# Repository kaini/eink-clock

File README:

# E-Ink Clock

For details read [the articles on my website](https://me.pushrax.com/e-ink-clock/).

## Build Instructions

To be able to successfully build the project you need the `inkscape` and
`magick` executable and a ARM GCC toolchain in your path. The resulting binary
is ready to be flashed onto the controller.

```
cd timekeeper
xargo build --target lpc1227-none-eabi --release
```

To execute the tests, run `cargo test`.

There are some features you might want to activate.

* `semihosted`: Enable debug output via the semihosting mechanism.
* `fake_time`: Do not wait for a valid DCF77 time, but just assume a hardcoded time value.
* `stay_awake`: Panic instead of going into Deep Power-Down mode.

## Warning

The PCB layout is not up to date!

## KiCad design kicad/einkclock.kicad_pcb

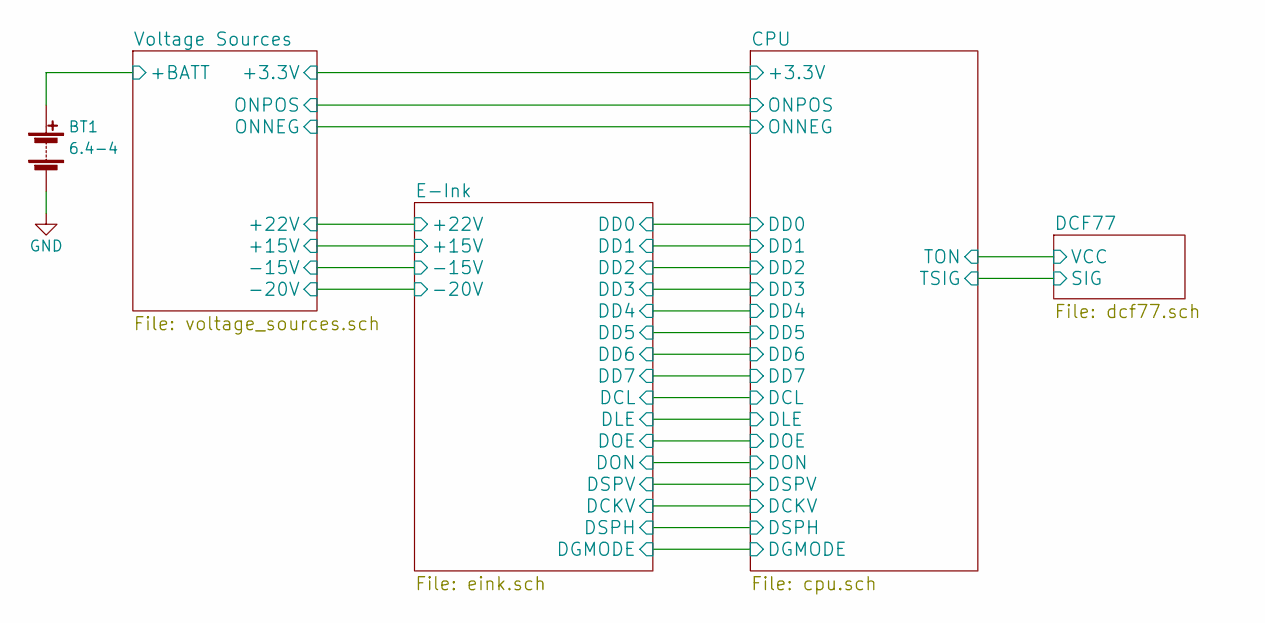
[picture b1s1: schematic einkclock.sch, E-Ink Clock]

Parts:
BT1: 6.4-4; WireConnection_1.00mmDrill

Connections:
GND: BT1.2 (-); also elsewhere on the board

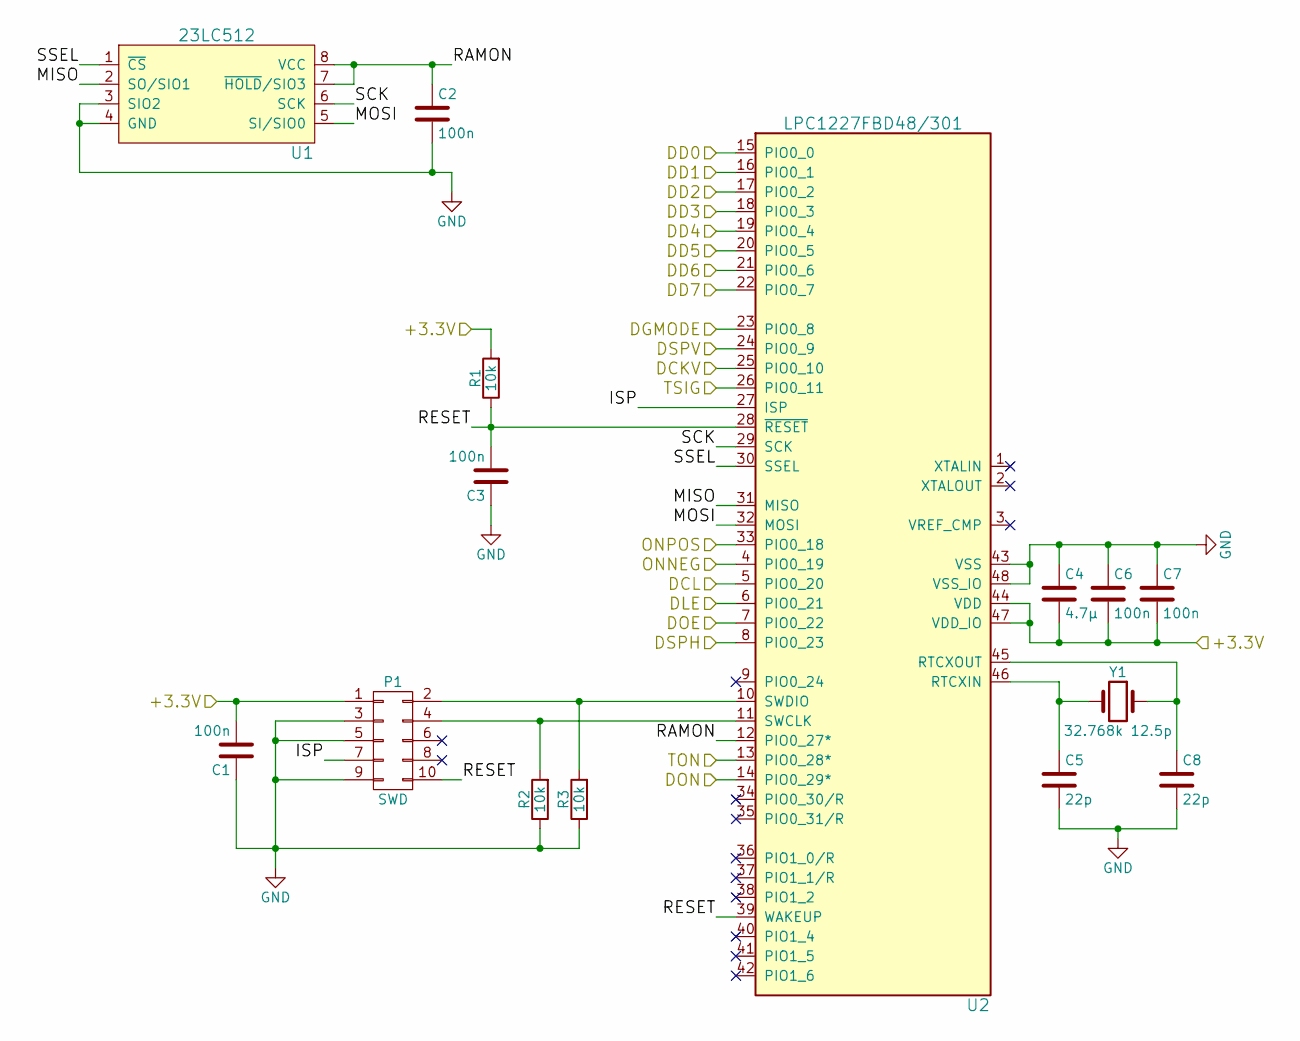
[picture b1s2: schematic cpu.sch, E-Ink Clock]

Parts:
C1, C2, C3, C6, C7: 100n; R_0805_HandSoldering
C4: 4.7µ; R_0805_HandSoldering
C5, C8: 22p; R_0805_HandSoldering
P1: SWD; IDC_Header_Straight_10pins
R1, R2, R3: 10k; R_0805_HandSoldering
U1: 23LC512; SOIC-8_3.9x4.9mm_Pitch1.27mm
U2: LPC1227FBD48/301; LQFP-48_7x7mm_Pitch0.5mm
Y1: 32.768k 12.5p; Crystal_Lying_1

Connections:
/CPU/+3.3V: C1.2, C4.2, C6.2, C7.2, P1.1, R1.2, U2.44 (VDD), U2.47 (VDD_IO); also elsewhere on the board
/CPU/DCKV: U2.25 (PIO0_10); also elsewhere on the board
/CPU/DCL: U2.5 (PIO0_20); also elsewhere on the board
/CPU/DD0: U2.15 (PIO0_0); also elsewhere on the board
/CPU/DD1: U2.16 (PIO0_1); also elsewhere on the board
/CPU/DD2: U2.17 (PIO0_2); also elsewhere on the board
/CPU/DD3: U2.18 (PIO0_3); also elsewhere on the board
/CPU/DD4: U2.19 (PIO0_4); also elsewhere on the board
/CPU/DD5: U2.20 (PIO0_5); also elsewhere on the board
/CPU/DD6: U2.21 (PIO0_6); also elsewhere on the board
/CPU/DD7: U2.22 (PIO0_7); also elsewhere on the board
/CPU/DGMODE: U2.23 (PIO0_8); also elsewhere on the board
/CPU/DLE: U2.6 (PIO0_21); also elsewhere on the board
/CPU/DOE: U2.7 (PIO0_22); also elsewhere on the board
/CPU/DON: U2.14 (PIO0_29*); also elsewhere on the board
/CPU/DSPH: U2.8 (PIO0_23); also elsewhere on the board
/CPU/DSPV: U2.24 (PIO0_9); also elsewhere on the board
/CPU/ISP: P1.7, U2.27 (ISP)
/CPU/MISO: U1.2 (SO/SIO1), U2.31 (MISO)
/CPU/MOSI: U1.5 (SI/SIO0), U2.32 (MOSI)
/CPU/ONPOS: U2.33 (PIO0_18); also elsewhere on the board
/CPU/RAMON: C2.1, U1.7 (~HOLD~/SIO3), U1.8 (VCC), U2.12 (PIO0_27*)
/CPU/RESET: C3.2, P1.10, R1.1, U2.28 (~RESET), U2.39 (WAKEUP)
/CPU/SCK: U1.6 (SCK), U2.29 (SCK)
/CPU/SSEL: U1.1 (~CS), U2.30 (SSEL)
/CPU/TON: U2.13 (PIO0_28*); also elsewhere on the board
/DCF77/SIG: U2.26 (PIO0_11); also elsewhere on the board
GND: C1.1, C2.2, C3.1, C4.1, C5.2, C6.1, C7.1, C8.2, P1.3, P1.5, P1.9, R2.1, R3.1, U1.3 (SIO2), U1.4 (GND), U2.43 (VSS), U2.48 (VSS_IO); also elsewhere on the board
unnamed: C5.1, U2.46 (RTCXIN), Y1.2
unnamed: C8.1, U2.45 (RTCXOUT), Y1.1
unnamed: P1.2, R3.2, U2.10 (SWDIO)
unnamed: P1.4, R2.2, U2.11 (SWCLK)

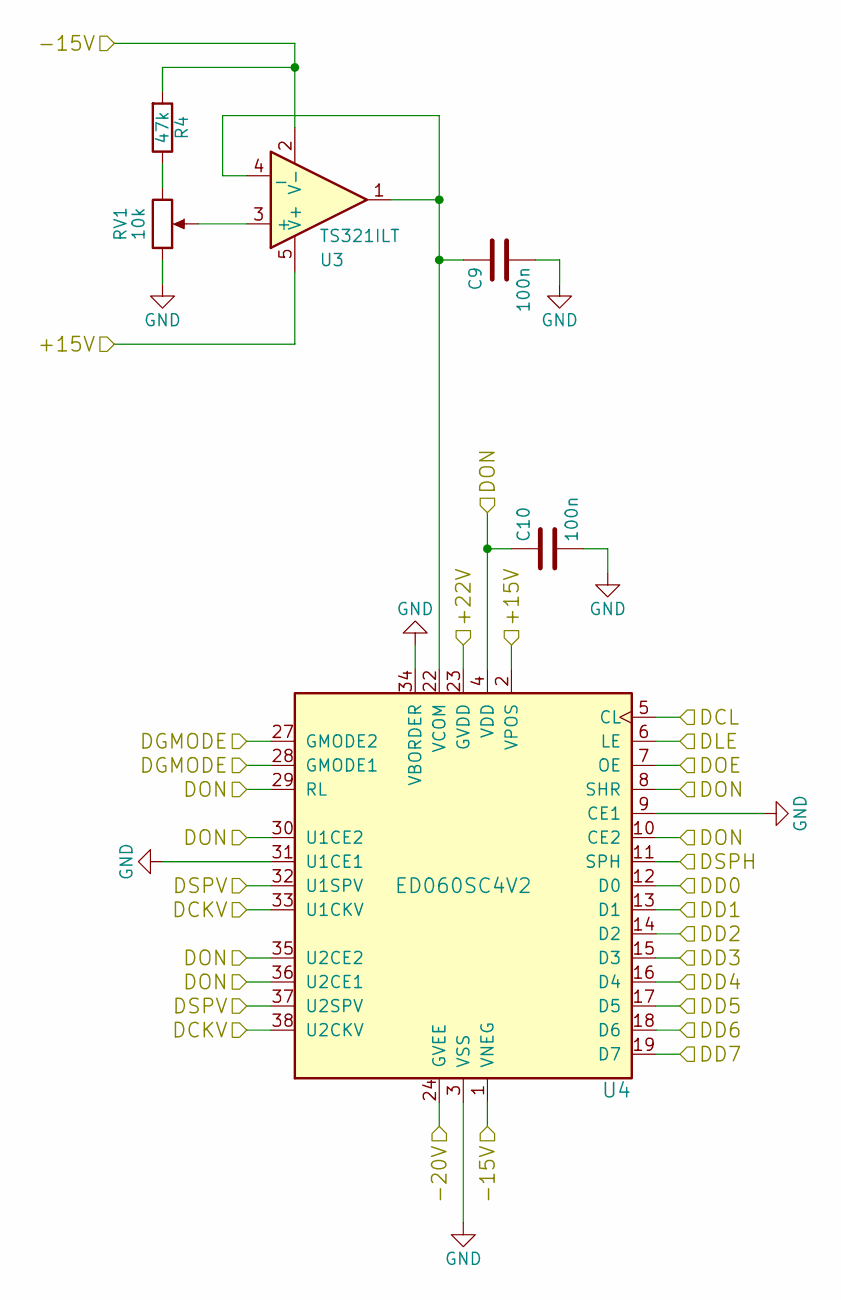
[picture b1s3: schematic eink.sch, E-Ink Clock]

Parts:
C9, C10: 100n; R_0805_HandSoldering
R4: 47k; R_0805_HandSoldering
RV1: 10k; Potentiometer_Trimmer_Vishay_TS53YL
U3: TS321ILT; SOT-23-5_HandSoldering
U4: ED060SC4V2; Hirose_FH26-39S-0.3SHW

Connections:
/CPU/DCKV: U4.33 (U1CKV), U4.38 (U2CKV); also elsewhere on the board
/CPU/DCL: U4.5 (CL); also elsewhere on the board
/CPU/DD0: U4.12 (D0); also elsewhere on the board
/CPU/DD1: U4.13 (D1); also elsewhere on the board
/CPU/DD2: U4.14 (D2); also elsewhere on the board
/CPU/DD3: U4.15 (D3); also elsewhere on the board
/CPU/DD4: U4.16 (D4); also elsewhere on the board
/CPU/DD5: U4.17 (D5); also elsewhere on the board
/CPU/DD6: U4.18 (D6); also elsewhere on the board
/CPU/DD7: U4.19 (D7); also elsewhere on the board
/CPU/DGMODE: U4.27 (GMODE2), U4.28 (GMODE1); also elsewhere on the board
/CPU/DLE: U4.6 (LE); also elsewhere on the board
/CPU/DOE: U4.7 (OE); also elsewhere on the board
/CPU/DON: C10.1, U4.4 (VDD), U4.8 (SHR), U4.10 (CE2), U4.29 (RL), U4.30 (U1CE2), U4.35 (U2CE2), U4.36 (U2CE1); also elsewhere on the board
/CPU/DSPH: U4.11 (SPH); also elsewhere on the board
/CPU/DSPV: U4.32 (U1SPV), U4.37 (U2SPV); also elsewhere on the board
/E-Ink/+15V: U3.5 (V+), U4.2 (VPOS); also elsewhere on the board
/E-Ink/+22V: U4.23 (GVDD); also elsewhere on the board
/E-Ink/-15V: R4.2, U3.2 (V-), U4.1 (VNEG); also elsewhere on the board
/E-Ink/-20V: U4.24 (GVEE); also elsewhere on the board
GND: C9.2, C10.2, RV1.1, U4.3 (VSS), U4.9 (CE1), U4.31 (U1CE1), U4.34 (VBORDER); also elsewhere on the board
unnamed: C9.1, U3.1, U3.4 (_), U4.22 (VCOM)
unnamed: R4.1, RV1.3
unnamed: RV1.2, U3.3 (+)

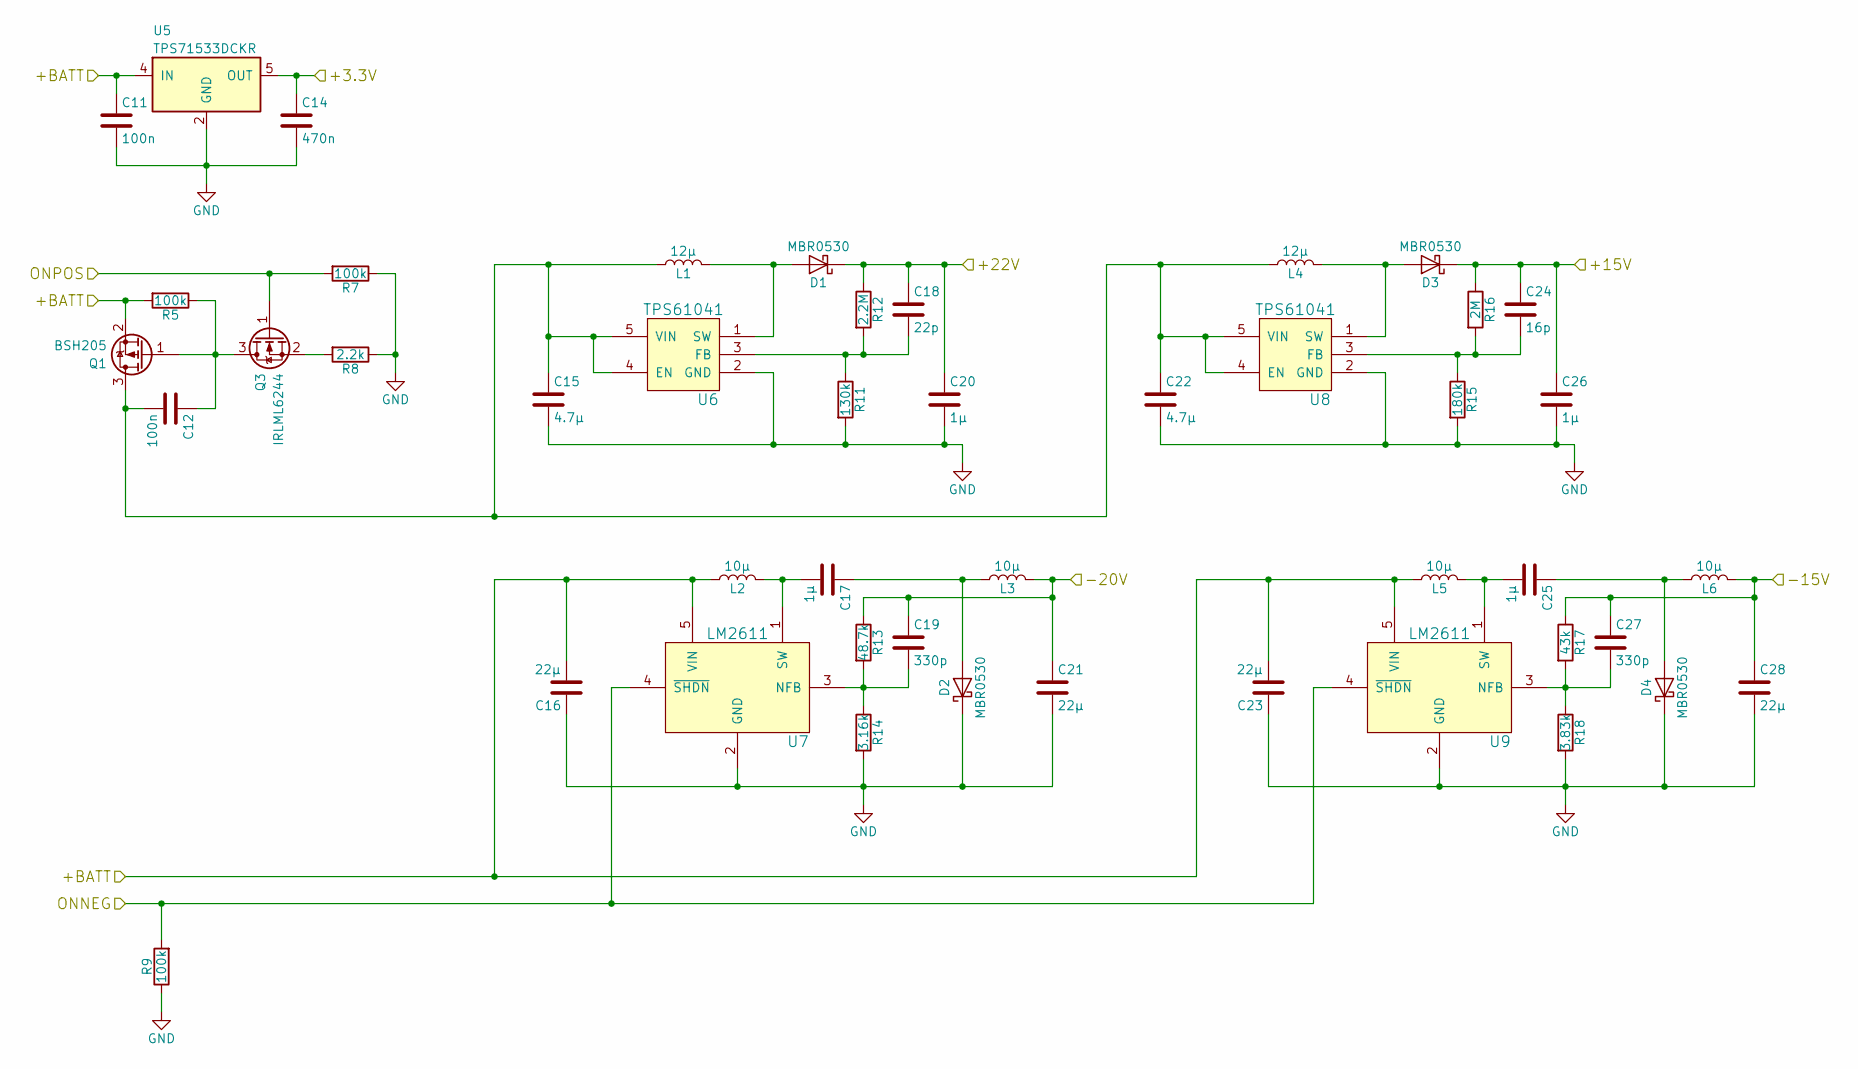
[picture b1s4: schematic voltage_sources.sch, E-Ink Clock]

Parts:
C11, C12: 100n; R_0805_HandSoldering
C14: 470n; R_0805_HandSoldering
C15, C22: 4.7µ; R_0805_HandSoldering
C16, C21, C23, C28: 22µ; R_0805_HandSoldering
C17, C20, C25, C26: 1µ; R_0805_HandSoldering
C18: 22p; R_0805_HandSoldering
C19, C27: 330p; R_0805_HandSoldering
C24: 16p; R_0805_HandSoldering
D1, D2, D3, D4: MBR0530; D_SOD-123
L1, L4: 12µ; Bourns_Inductor_SDR0703
L2, L3, L5, L6: 10µ; Inductor_TAIYO_YUDEN_3225
Q1: BSH205; SOT-23_Handsoldering
Q3: IRLML6244; SOT-23_Handsoldering
R5, R7, R9: 100k; R_0805_HandSoldering
R8: 2.2k; R_0805_HandSoldering
R11: 130k; R_0805_HandSoldering
R12: 2.2M; R_0805_HandSoldering
R13: 48.7k; R_0805_HandSoldering
R14: 3.16k; R_0805_HandSoldering
R15: 180k; R_0805_HandSoldering
R16: 2M; R_0805_HandSoldering
R17: 43k; R_0805_HandSoldering
R18: 3.83k; R_0805_HandSoldering
U5: TPS71533DCKR; SOT-353_SC-70-5_Handsoldering
U6, U8: TPS61041; SOT-23-5_HandSoldering
U7, U9: LM2611; SOT-23-5_HandSoldering

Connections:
/CPU/+3.3V: C14.1, U5.5 (OUT); also elsewhere on the board
/CPU/ONPOS: Q3.1 (G), R7.2; also elsewhere on the board
/E-Ink/+15V: C24.1, C26.1, D3.1 (K), R16.1; also elsewhere on the board
/E-Ink/+22V: C18.1, C20.1, D1.1 (K), R12.1; also elsewhere on the board
/E-Ink/-15V: C27.1, C28.1, L6.2, R17.1; also elsewhere on the board
/E-Ink/-20V: C19.1, C21.1, L3.2, R13.1; also elsewhere on the board
GND: C11.2, C14.2, C15.2, C16.1, C20.2, C21.2, C22.2, C23.1, C26.2, C28.2, D2.1 (K), D4.1 (K), R7.1, R8.1, R9.1, R11.2, R14.2, R15.2, R18.2, U5.2 (GND), U6.2 (GND), U7.2 (GND), U8.2 (GND), U9.2 (GND); also elsewhere on the board
unnamed: C12.1, Q1.1 (G), Q3.3 (D), R5.1
unnamed: C12.2, C15.1, C22.1, L1.1, L4.1, Q1.3 (D), U6.4 (EN), U6.5 (VIN), U8.4 (EN), U8.5 (VIN)
unnamed: C17.1, D2.2 (A), L3.1
unnamed: C17.2, L2.2, U7.1 (SW)
unnamed: C18.2, R11.1, R12.2, U6.3 (FB)
unnamed: C19.2, R13.2, R14.1, U7.3 (NFB)
unnamed: C24.2, R15.1, R16.2, U8.3 (FB)
unnamed: C25.1, D4.2 (A), L6.1
unnamed: C25.2, L5.2, U9.1 (SW)
unnamed: C27.2, R17.2, R18.1, U9.3 (NFB)
unnamed: D1.2 (A), L1.2, U6.1 (SW)
unnamed: D3.2 (A), L4.2, U8.1 (SW)
unnamed: Q3.2 (S), R8.2

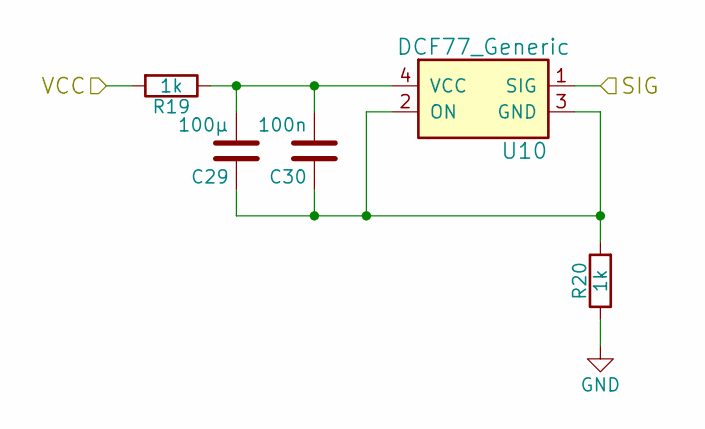
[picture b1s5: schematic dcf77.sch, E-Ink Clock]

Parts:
C29: 100µ; R_1206_HandSoldering
C30: 100n; R_0805_HandSoldering
R19, R20: 1k; R_0805_HandSoldering
U10: DCF77_Generic; Reichelt_DCF77_Module

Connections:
/CPU/TON: R19.2; also elsewhere on the board
/DCF77/SIG: U10.1 (SIG); also elsewhere on the board
GND: R20.1; also elsewhere on the board
unnamed: C29.1, C30.1, R20.2, U10.2 (ON), U10.3 (GND)
unnamed: C29.2, C30.2, R19.1, U10.4 (VCC)

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
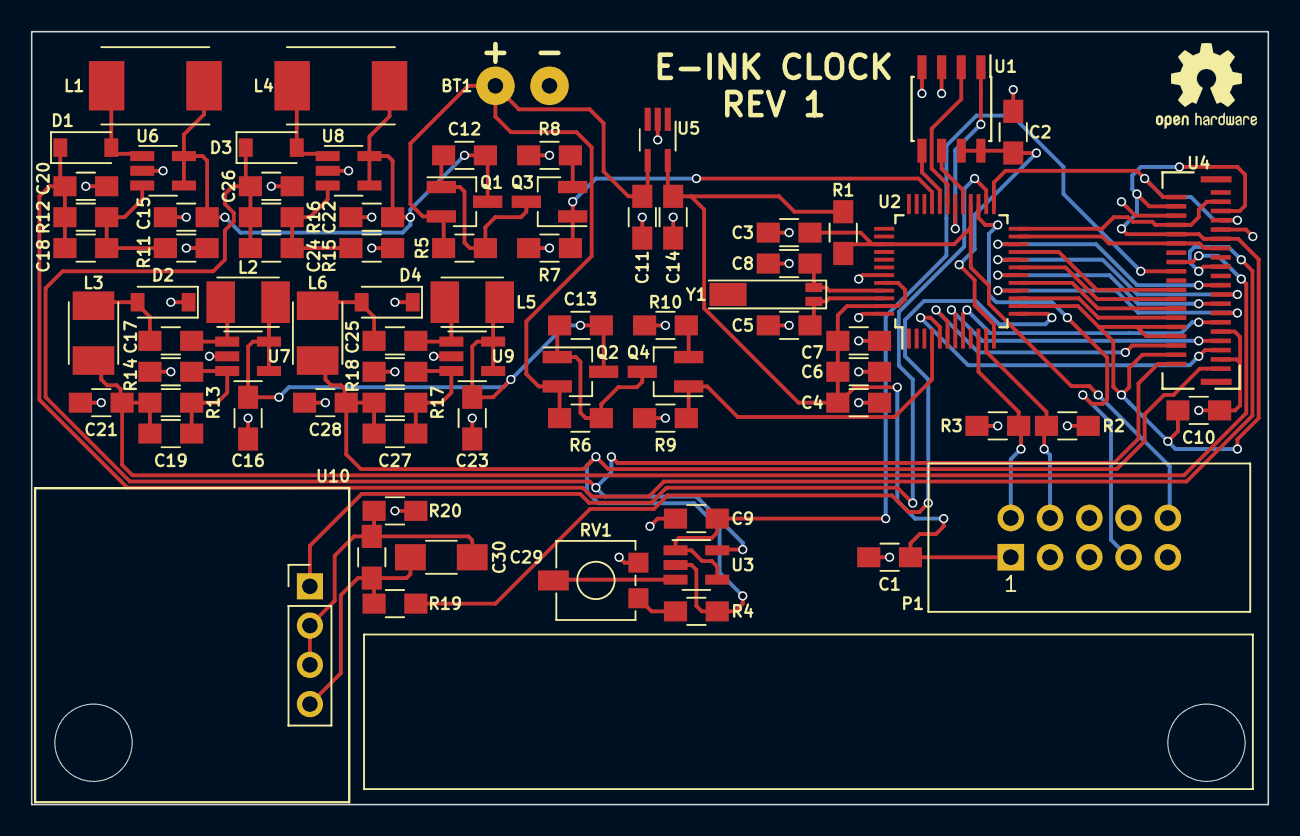
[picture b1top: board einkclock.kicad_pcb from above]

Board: 2 copper layers, 80.0 x 50.0 mm, 78 parts (0 on the bottom side), 59 nets.

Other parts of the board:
C13: 100n; R_0805_HandSoldering
Q2: BSH205; SOT-23_Handsoldering
Q4: IRLML6244; SOT-23_Handsoldering
R6: 100k; R_0805_HandSoldering
R10: 2.2k; R_0805_HandSoldering

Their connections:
GND: R10.1; also elsewhere on the board
unnamed: C13.1, Q2.1, Q4.3, R6.1
unnamed: Q4.2, R10.2

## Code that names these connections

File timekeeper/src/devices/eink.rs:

use rawhw::ioconfig::Pullup;
use devices::cpu::usleep;

// ONPOS
use rawhw::gpio::gpio0 as onpos_gpio;
use rawhw::ioconfig::pio0_18 as onpos_ioconfig;
const ONPOS_BIT: u32 = 18;

// ONNEG
use rawhw::gpio::gpio0 as onneg_gpio;
use rawhw::ioconfig::pio0_19 as onneg_ioconfig;
const ONNEG_BIT: u32 = 19;

// DON
use rawhw::gpio::gpio0 as don_gpio;
use rawhw::ioconfig::pio0_29 as don_ioconfig;
const DON_BIT: u32 = 29;

// DD
use rawhw::gpio::gpio0 as dd_gpio;
use rawhw::ioconfig::pio0_0 as dd0_ioconfig;
use rawhw::ioconfig::pio0_1 as dd1_ioconfig;
use rawhw::ioconfig::pio0_2 as dd2_ioconfig;
use rawhw::ioconfig::pio0_3 as dd3_ioconfig;
use rawhw::ioconfig::pio0_4 as dd4_ioconfig;
use rawhw::ioconfig::pio0_5 as dd5_ioconfig;
use rawhw::ioconfig::pio0_6 as dd6_ioconfig;
use rawhw::ioconfig::pio0_7 as dd7_ioconfig;
const DD_SHIFT: u32 = 0;

// DCL
use rawhw::gpio::gpio0 as dcl_gpio;
use rawhw::ioconfig::pio0_20 as dcl_ioconfig;
const DCL_BIT: u32 = 20;

// DLE
use rawhw::gpio::gpio0 as dle_gpio;
use rawhw::ioconfig::pio0_21 as dle_ioconfig;
const DLE_BIT: u32 = 21;

// DOE
use rawhw::gpio::gpio0 as doe_gpio;
use rawhw::ioconfig::pio0_22 as doe_ioconfig;
const DOE_BIT: u32 = 22;

// DGMODE
use rawhw::gpio::gpio0 as dgmode_gpio;
use rawhw::ioconfig::pio0_8 as dgmode_ioconfig;
const DGMODE_BIT: u32 = 8;

// DSPV
use rawhw::gpio::gpio0 as dspv_gpio;
use rawhw::ioconfig::pio0_9 as dspv_ioconfig;
const DSPV_BIT: u32 = 9;

// DCKV
use rawhw::gpio::gpio0 as dckv_gpio;
const DCKV_BIT: u32 = 10;

// DSPH
use rawhw::gpio::gpio0 as dsph_gpio;
use rawhw::ioconfig::pio0_23 as dsph_ioconfig;
const DSPH_BIT: u32 = 23;

const WHITE: u8 = 0b10;
const BLACK: u8 = 0b01;

pub const SCANLINES: usize = 600;
pub const SCANLINE_WIDTH: usize = 800;
pub const SCANLINE_BYTES: usize = SCANLINE_WIDTH / 8;
static mut BUFFER: [u8; SCANLINE_BYTES] = [0; SCANLINE_BYTES];

macro_rules! setup_output {
    ($ioconfig:ident, $gpio:ident, $bit:expr) => ({
        $ioconfig::mode::set(Pullup::Disabled);
        $gpio::dir::set_bit($bit);
        $gpio::clr::set(1 << $bit);
    });
}

pub unsafe fn early_init() {
    setup_output!(onpos_ioconfig, onpos_gpio, ONPOS_BIT);
    setup_output!(onneg_ioconfig, onneg_gpio, ONNEG_BIT);
    setup_output!(don_ioconfig, don_gpio, DON_BIT);
}

pub unsafe fn init() {
    don_ioconfig::drv::set(true);
    setup_output!(dd0_ioconfig, dd_gpio, DD_SHIFT + 0);
    setup_output!(dd1_ioconfig, dd_gpio, DD_SHIFT + 1);
    setup_output!(dd2_ioconfig, dd_gpio, DD_SHIFT + 2);
    setup_output!(dd3_ioconfig, dd_gpio, DD_SHIFT + 3);
    setup_output!(dd4_ioconfig, dd_gpio, DD_SHIFT + 4);
    setup_output!(dd5_ioconfig, dd_gpio, DD_SHIFT + 5);
    setup_output!(dd6_ioconfig, dd_gpio, DD_SHIFT + 6);
    setup_output!(dd7_ioconfig, dd_gpio, DD_SHIFT + 7);
    setup_output!(dcl_ioconfig, dcl_gpio, DCL_BIT);
    setup_output!(dle_ioconfig, dle_gpio, DLE_BIT);
    setup_output!(doe_ioconfig, doe_gpio, DOE_BIT);
    setup_output!(dgmode_ioconfig, dgmode_gpio, DGMODE_BIT);
    setup_output!(dspv_ioconfig, dspv_gpio, DSPV_BIT);
    // This pin does not have a pullup, therefore the setup_output code does not apply.
    dckv_gpio::dir::set_bit(DCKV_BIT);
    dckv_gpio::clr::set(1 << DCKV_BIT);
    setup_output!(dsph_ioconfig, dsph_gpio, DSPH_BIT);
}

unsafe fn enable() {
    don_gpio::set::set(1 << DON_BIT);
    usleep(100);
    onneg_gpio::set::set(1 << ONNEG_BIT);
    usleep(1000);
    onpos_gpio::set::set(1 << ONPOS_BIT);
    usleep(1000);
}

unsafe fn disable() {
    onpos_gpio::clr::set(1 << ONPOS_BIT);
    usleep(1000);
    onneg_gpio::clr::set(1 << ONNEG_BIT);
    usleep(1000);
    don_gpio::clr::set(1 << DON_BIT);
    usleep(100);
}

unsafe fn draw_mode_on() {
    dgmode_gpio::set::set(1 << DGMODE_BIT);
    dckv_gpio::set::set(1 << DCKV_BIT);
    dsph_gpio::set::set(1 << DSPH_BIT);
    for _ in 0..20 {
        usleep(10000);
    }
}

unsafe fn draw_mode_off() {
    dd_gpio::clr::set(0xFF << DD_SHIFT);
    dcl_gpio::clr::set(1 << DCL_BIT);
    dle_gpio::clr::set(1 << DLE_BIT);
    doe_gpio::clr::set(1 << DOE_BIT);
    dgmode_gpio::clr::set(1 << DGMODE_BIT);
    dspv_gpio::clr::set(1 << DSPV_BIT);
    dckv_gpio::clr::set(1 << DCKV_BIT);
    dsph_gpio::clr::set(1 << DSPH_BIT);
}

unsafe fn advance_line() {
    dckv_gpio::clr::set(1 << DCKV_BIT);
    usleep(1);
    dckv_gpio::set::set(1 << DCKV_BIT);
    usleep(1);
}

unsafe fn begin_frame() {
    dspv_gpio::set::set(1 << DSPV_BIT);
    usleep(500);
    dspv_gpio::clr::set(1 << DSPV_BIT);
    usleep(1);
    dckv_gpio::clr::set(1 << DCKV_BIT);
    usleep(25);
    dckv_gpio::set::set(1 << DCKV_BIT);
    usleep(1);
    dspv_gpio::set::set(1 << DSPV_BIT);
    usleep(25);

    // For some reason I have to advance 3 times to fill the whole screen
    advance_line();
    advance_line();
    advance_line();
}

unsafe fn end_frame() {
}

unsafe fn begin_line() {
    // This line is only required if you need a long time to calculate each scanline (1 of 2)
    //doe_gpio::set::set(1 << DOE_BIT);
    dsph_gpio::clr::set(1 << DSPH_BIT);
    usleep(1);
}

unsafe fn end_line() {
    dsph_gpio::set::set(1 << DSPH_BIT);
    usleep(1);

    dcl_gpio::set::set(1 << DCL_BIT);
    dckv_gpio::clr::set(1 << DCKV_BIT);
    usleep(1);
    dcl_gpio::clr::set(1 << DCL_BIT);
    usleep(1);
    dckv_gpio::set::set(1 << DCKV_BIT);
    usleep(1);
    doe_gpio::clr::set(1 << DOE_BIT);
    // This time controls the load and therefore might induce a hearable frequency
    // on the inductors of a switching power supply.
    // usleep(1);  
    doe_gpio::set::set(1 << DOE_BIT);
    usleep(1);
    dle_gpio::set::set(1 << DLE_BIT);
    usleep(1);
    dle_gpio::clr::set(1 << DLE_BIT);
    usleep(1);
    
    // This line is only required if you need a long time to calculate each scanline (2 of 2)
    //doe_gpio::clr::set(1 << DOE_BIT);
}

// Use the constants NOOP, WHITE, BLACK.
unsafe fn set_four_pixels(pixels: &[u8; 4]) {
    dd_gpio::mask::set(!(0xFF << DD_SHIFT));
    dd_gpio::out::set((((pixels[0] << 6) | (pixels[1] << 4) | (pixels[2] << 2) | pixels[3]) as u32) << DD_SHIFT);
    dd_gpio::mask::set(0);
    dcl_gpio::set::set(1 << DCL_BIT);
    usleep(1);
    dcl_gpio::clr::set(1 << DCL_BIT);
    usleep(1);
}

pub fn render<Draw>(draw: &Draw)
        where Draw: Fn(usize, &mut [u8; SCANLINE_BYTES]) {
    unsafe {
        enable();
        draw_mode_on();

        begin_frame();
        for scanline in 0..SCANLINES {
            draw(scanline, &mut BUFFER);
            let mut buffer_byte = 0;

            begin_line();
            for _ in 0..(SCANLINE_WIDTH / 8) {
                set_four_pixels(&[
                    if (BUFFER[buffer_byte] & (1 << 0)) != 0 { BLACK } else { WHITE },
                    if (BUFFER[buffer_byte] & (1 << 1)) != 0 { BLACK } else { WHITE },
                    if (BUFFER[buffer_byte] & (1 << 2)) != 0 { BLACK } else { WHITE },
                    if (BUFFER[buffer_byte] & (1 << 3)) != 0 { BLACK } else { WHITE },
                ]);
                set_four_pixels(&[
                    if (BUFFER[buffer_byte] & (1 << 4)) != 0 { BLACK } else { WHITE },
                    if (BUFFER[buffer_byte] & (1 << 5)) != 0 { BLACK } else { WHITE },
                    if (BUFFER[buffer_byte] & (1 << 6)) != 0 { BLACK } else { WHITE },
                    if (BUFFER[buffer_byte] & (1 << 7)) != 0 { BLACK } else { WHITE },
                ]);
                buffer_byte += 1;
            }
            end_line();
        }
        end_frame();

        draw_mode_off();
        disable();
    }
}

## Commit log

2017-02-13 Add C project for the microcontroller
2017-02-13 Add new bookmark for LPC clock selection
2017-02-13 Add LPC1227 datasheet
2017-02-14 Implement first low level DCF77 implementation
2017-02-14 Refactor SYSCON to not use bit magic
2017-02-14 Use newlib, cleanup debug-log and cleanup main
2017-02-15 First simple Rust build
2017-02-15 Refine Rust setup
2017-02-16 Port to Rust
2017-02-16 Implement DCF77 parsing
2017-02-16 Add andmask feature to register macros
2017-02-17 Add basic RTC clock functionallity
2017-02-17 Add fixes to KiCad schematc
2017-02-19 Start PCB routing
2017-02-19 Change optimization level to 's' and make core dependency explicit
2017-02-19 Implement advanced date and time functionallity
2017-02-19 Remove redundand KiCad files
2017-02-20 Cleanup KiCad files and route board
2017-02-20 Add ground layer
2017-03-07 Remove direct C dependency
2017-03-07 Remove C startup code
2017-03-08 Remove datasheets
2017-03-09 Make test, debug and release build working again
2017-03-09 Fix linker script
2017-03-09 Remove libc
2017-03-09 Make it work again (stack overflow)
2017-03-16 Working eink
2017-03-16 Working eink display
2017-03-16 Render watch
2017-03-16 Clean up build process
2017-03-16 Move stack to the beginning of the RAM
2017-03-16 Add graphics rendering
2017-03-17 Text rendering
2017-03-17 Improve rendering
2017-03-17 Fix build script
2017-03-18 Make DCF77 functionallity async
2017-03-19 First working sync
2017-03-19 Fix and change build process
2017-03-19 Slow line rendering
2017-03-20 Enable debug assertions in the debug build
2017-03-20 Remove builtins crate
2017-03-22 Render time :)
2017-03-22 Fix some warnings
2017-03-22 Add resync
2017-03-22 Fix kerning
2017-03-22 Refactor eink
2017-03-23 First improvement of rendering time
2017-03-23 Fix typo
2017-03-24 Add deep power down stuff
2017-03-25 Change RTC to seconds
2017-03-26 Fixup schematic
2017-03-26 Schematic fixes
2017-03-29 Rework schematic
2017-03-30 Finish schematic
2017-03-30 Set most footprints
2017-03-30 Finish footprints
2017-04-01 First routing
2017-04-02 Cleanups
2017-04-03 Adjustments
2017-04-03 Add BOM
2017-04-04 Finish BOM and fix PCB according to the parts
2017-04-04 Refine BOM
2017-04-04 Make BOM friendlier for some BOM parsers
2017-05-03 Make it work again
2017-05-03 Improve init code
2017-05-04 Render to RAM
2017-05-04 Fix LM2611 switch
2017-05-04 Rasterize instead of trace
2017-05-04 Add single byte caching
2017-05-05 Improve E-Ink timings
2017-05-05 Nice <> when syncthing time.
2017-05-07 Clean up initialization
2017-05-10 Update date
2017-05-11 Add readme and license
2017-05-11 Trigger mirror
2017-05-11 Rename README for github
2017-06-30 Fix rendering artefact
